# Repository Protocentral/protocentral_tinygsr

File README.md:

# ProtoCentral tinyGSR 

## Don't have one? [Buy it here](https://protocentral.com/product/protocentral-tinygsr-breakout-board-qwiic-stemma-qt/)

Protocentral tinyGSR is a [Galvanic Skin Response (GSR) / Electrodermal Activity (EDA)](https://en.wikipedia.org/wiki/Electrodermal_activity) measurement breakout board that allows you to measure and track your physiological responses in real time. GSR measures the changes in electrical conductivity / Electrodermal acivity of the skin, providing valuable insights into a person's emotional state and stress levels. When a person is emotionally aroused or stressed, their sweat gland activity increases, which can be measured as changes in the electrical conductivity of the skin. 

tinyGSR contains onboard analog op-amps to measure this change in resistance and helps you to easily interface this with your microcontroller system using just a digital interface. tinyGSR can be a powerful tool for anyone looking to better understand their body and emotions. The tinyGSR has Qwiic compatible connector, in addition to standard breakout headers to just plug it into any compatible board with no soldering required. 

## Hardware Setup

Connection with the Arduino board is as follows:
 
 |tinyGSR pin label | Arduino Connection  |Pin Function      |
 |:-----------------: |:-----------------:|:----------------:|
 | SDA              | A4                  |  Serial Data     |
 | SCL              | A5                  |  Serial Clock    |
 | Vin              | +5V                 |  Power Supply    |
 | GND              | GND                 |  GND             |

Alternately you can connect using qwiic adaptor:

<center>

</center>

# Visualizing Output

## For further details, refer [the documentation on TinyGSR](https://docs.protocentral.com/getting-started-with-tinyGSR/)

License Information
===================

This product is open source! Both, our hardware and software are open source and licensed under the following licenses:

Hardware
---------

**All hardware is released under the [CERN-OHL-P v2](https://ohwr.org/cern_ohl_p_v2.txt)** license.

Copyright CERN 2020.

This source describes Open Hardware and is licensed under the CERN-OHL-P v2.

You may redistribute and modify this documentation and make products
using it under the terms of the CERN-OHL-P v2 (https:/cern.ch/cern-ohl).
This documentation is distributed WITHOUT ANY EXPRESS OR IMPLIED
WARRANTY, INCLUDING OF MERCHANTABILITY, SATISFACTORY QUALITY
AND FITNESS FOR A PARTICULAR PURPOSE. Please see the CERN-OHL-P v2
for applicable conditions

Software
--------

**All software is released under the MIT License(http://opensource.org/licenses/MIT).**

THE SOFTWARE IS PROVIDED "AS IS", WITHOUT WARRANTY OF ANY KIND, EXPRESS OR IMPLIED, INCLUDING BUT NOT LIMITED TO THE WARRANTIES OF MERCHANTABILITY, FITNESS FOR A PARTICULAR PURPOSE AND NONINFRINGEMENT. IN NO EVENT SHALL THE AUTHORS OR COPYRIGHT HOLDERS BE LIABLE FOR ANY CLAIM, DAMAGES OR OTHER LIABILITY, WHETHER IN AN ACTION OF CONTRACT, TORT OR OTHERWISE, ARISING FROM, OUT OF OR IN CONNECTION WITH THE SOFTWARE OR THE USE OR OTHER DEALINGS IN THE SOFTWARE.

Documentation
-------------
**All documentation is released under [Creative Commons Share-alike 4.0 International](http://creativecommons.org/licenses/by-sa/4.0/).**

You are free to:

* Share — copy and redistribute the material in any medium or format
* Adapt — remix, transform, and build upon the material for any purpose, even commercially.
The licensor cannot revoke these freedoms as long as you follow the license terms.

Under the following terms:

* Attribution — You must give appropriate credit, provide a link to the license, and indicate if changes were made. You may do so in any reasonable manner, but not in any way that suggests the licensor endorses you or your use.
* ShareAlike — If you remix, transform, or build upon the material, you must distribute your contributions under the same license as the original.

Please check [*LICENSE.md*](LICENSE.md) for detailed license descriptions.

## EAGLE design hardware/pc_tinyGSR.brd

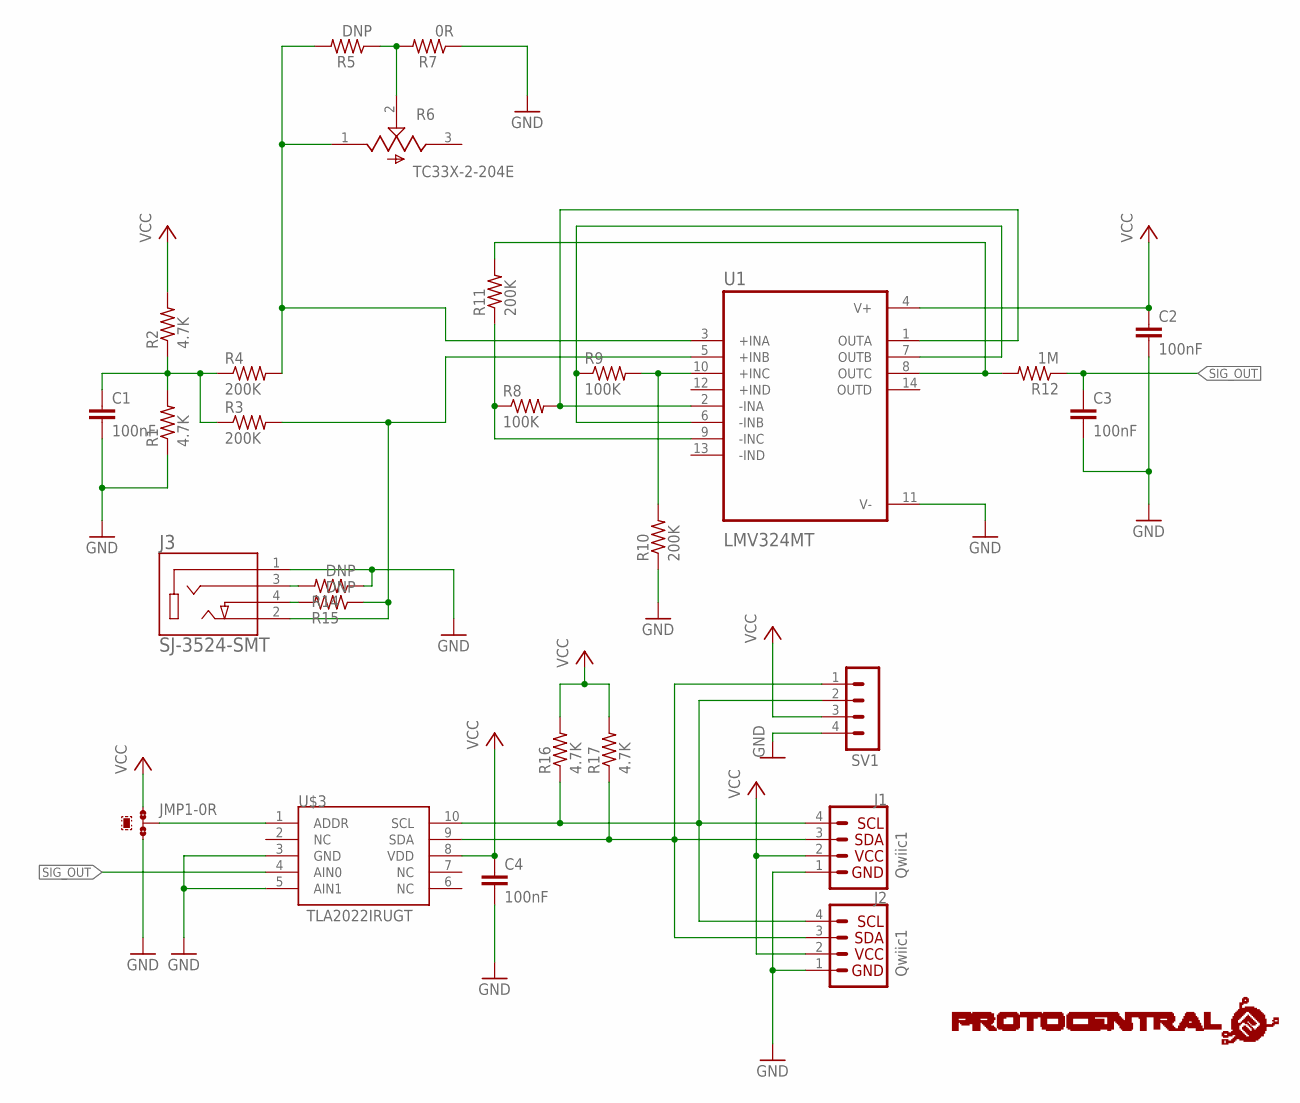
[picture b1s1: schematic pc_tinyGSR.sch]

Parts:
C1, C2, C3, C4: 100nF; C0402
J1, J2: Qwiic1; 1X04_1MM_RA
J3: SJ-3524-SMT; CUI_SJ-3524-SMT
JMP1: 0R-JUMPA; A0R-JMP
R1, R2, R16, R17: 4.7K; R0402
R3, R4, R10, R11: 200K; R0402
R5, R14, R15: DNP; R0402
R6: TC33X-2-204E; TRIM_TC33X-2-204E
R7: 0R; R0402
R8, R9: 100K; R0402
R12: 1M; R0402
SV1: MA04-1
U1: LMV324MT; SOP65P640X120-14N
U$1: PROTY_LOGO_WITH_TEXT; PROTY_WITH_TEXT
U$3: TLA2022IRUGT; QFN50P200X150X40-10N

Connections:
GND: C1.2, C2.2, C3.2, C4.2, J1.1, J2.1, J3.1, JMP1.3, R1.1, R7.1, R10.1, R14.1, SV1.4, U1.11 (V-), U$3.3 (GND), U$3.5 (AIN1)
unnamed: R5.1, R6.2 (W), R7.2
unnamed: J3.2, R3.2, R15.1, U1.5 (+INB)
unnamed: C1.1, R1.2, R2.1, R3.1, R4.1
unnamed: R8.1, R11.1, U1.9 (-INC)
unnamed: R4.2, R5.2, R6.1 (CCW), U1.3 (+INA)
unnamed: R8.2, U1.1 (OUTA), U1.2 (-INA)
unnamed: R9.1, U1.6 (-INB), U1.7 (OUTB)
unnamed: R9.2, R10.2, U1.10 (+INC)
unnamed: R11.2, R12.2, U1.8 (OUTC)
unnamed: JMP1.2, U$3.1 (ADDR)
unnamed: J1.4, J2.4, R16.1, SV1.2, U$3.10 (SCL)
unnamed: J1.3, J2.3, R17.1, SV1.1, U$3.9 (SDA)
unnamed: J3.3, R14.2
unnamed: J3.4, R15.2
SIG_OUT: C3.1, R12.1, U$3.4 (AIN0)
VCC: C2.1, C4.1, J1.2, J2.2, JMP1.1, R2.2, R16.2, R17.2, SV1.3, U1.4 (V+), U$3.8 (VDD)

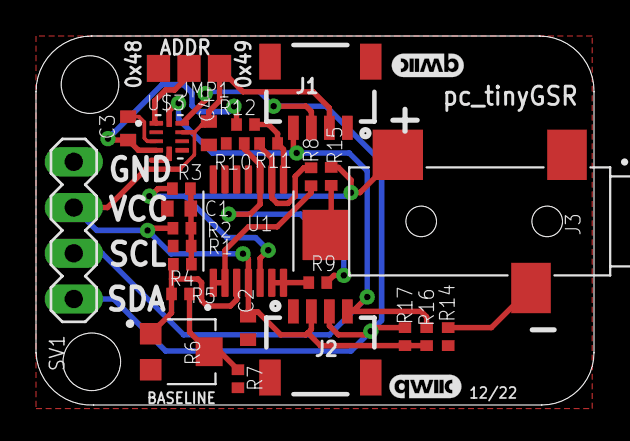
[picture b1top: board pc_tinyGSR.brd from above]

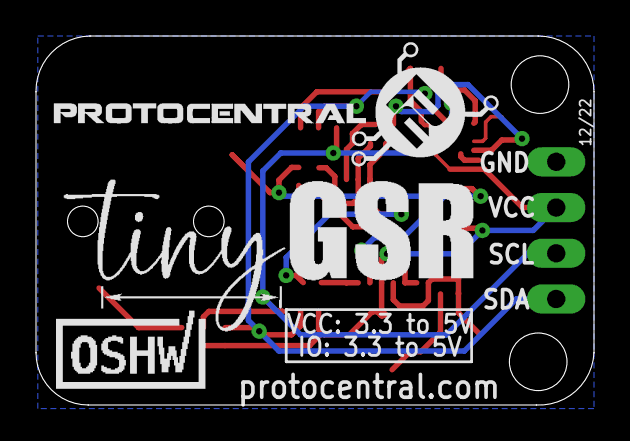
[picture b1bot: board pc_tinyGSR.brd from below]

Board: 4 copper layers, 31.0 x 20.5 mm, 32 parts (3 on the bottom side), 17 nets.

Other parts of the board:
LOGO1, LOGO3: QWIIC_LOGO_4MM; QWIIC_4MM
U$2: CERT-SMALL-SILK
U$4: TINYGSR

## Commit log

2023-01-02 Added openview support
2023-01-02 Added FIR filter with OpenView
2023-01-02 Reformatted
2023-01-04 Added assests for Readme
2023-01-05 Cleaned up Github repo
2023-01-05 Create hardware
2023-01-05 Create sch
2025-04-10 Readme updated and workflow added
2025-04-10 readme updated
2025-04-11 readme updated with gif

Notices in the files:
README.md:
CC-BY-SA-4.0
parts and their libraries:
SparkFun-Aesthetics: Licensing: Creative Commons ShareAlike 4.0 International - https://creativecommons.org/licenses/by-sa/4.0
